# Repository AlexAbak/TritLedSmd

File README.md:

# TritLedSmd
Индикатор трита компактный

Документация и обсуждение https://myweek-end.ru/trit/tritledsmd

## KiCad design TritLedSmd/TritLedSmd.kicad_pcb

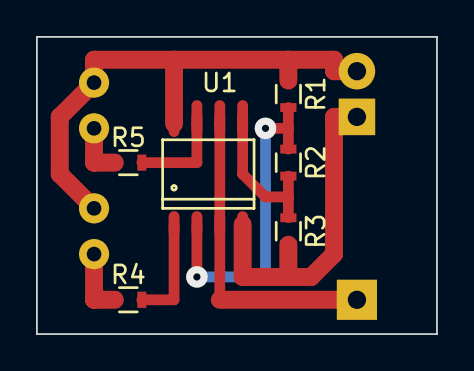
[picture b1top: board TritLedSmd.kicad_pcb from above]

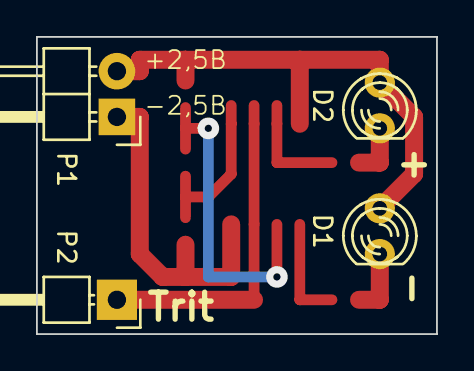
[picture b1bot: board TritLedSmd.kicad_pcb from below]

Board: 2 copper layers, 22.2 x 16.5 mm, 10 parts (4 on the bottom side), 9 nets.

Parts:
D1: -; LED-3MM
D2: +; LED-3MM
P1: Power; Pin_Header_Angled_1x02
P2: In; Pin_Header_Angled_1x01
R1, R2, R3: 4.7KΩ; R_0603
R4, R5: 220Ω; R_0603
U1: LM393; SO-8

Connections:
unnamed: D1.1, D2.1, P1.2, R1.1, U1.8
unnamed: D1.2, R4.1
unnamed: D2.2, R5.1
unnamed: P1.1, R3.2, U1.4
unnamed: P2.1, U1.3, U1.6
unnamed: R1.2, R2.1, U1.2
unnamed: R2.2, R3.1, U1.5
unnamed: R4.2, U1.1
unnamed: R5.2, U1.7

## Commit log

2015-04-26 Заливка схемы
2015-04-27 3D вид и исправление расположения элементов
2015-04-27 Косметические правки изображений
